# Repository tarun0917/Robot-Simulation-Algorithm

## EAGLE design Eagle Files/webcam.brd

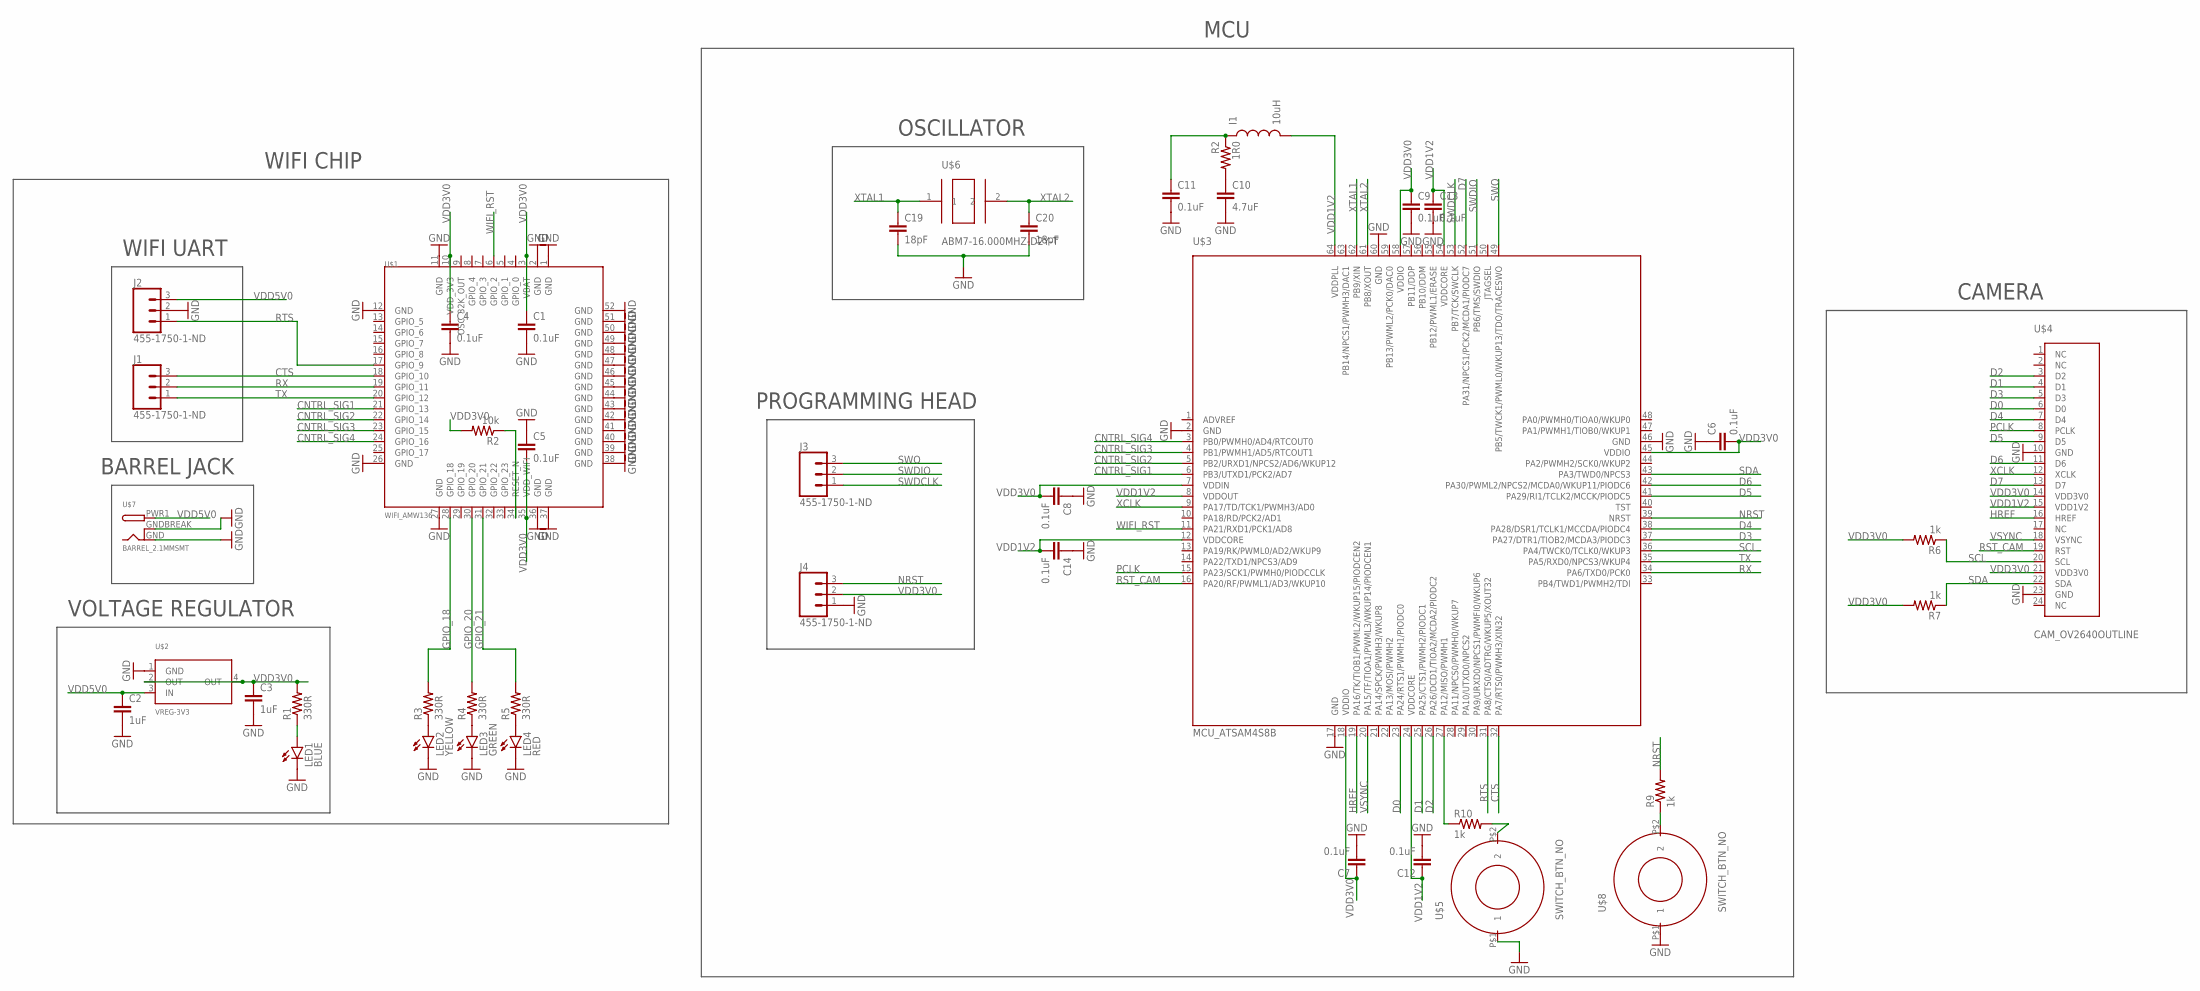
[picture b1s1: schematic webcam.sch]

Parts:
1R0: R2; 0805
C1, C4, C5, C6, C7, C8, C9, C11, C12, C13, C14: 0.1uF; 0805
C2, C3: 1uF; 0805
C10: 4.7uF; 0805
C19, C20: 18pF; 0805
I1: 10uH; 0805
J1, J2, J3, J4: 455-1750-1-ND; 1X03
LED1: BLUE; LED-0603
LED2: YELLOW; LED-0603
LED3: GREEN; LED-0603
LED4: RED; LED-0603
R1, R3, R4, R5: 330R; 0805
R2: 10k; 0805
R6, R7, R9, R10: 1k; 0805
U$1: WIFI_AMW136; AMW136
U$2: VREG-3V3; R-PDSO-G4_TI
U$3: MCU_ATSAM4S8B; QFP50P1200X1200X160-64N
U$4: CAM_OV2640OUTLINE; CAM_CONN
U$5, U$8: SWITCH_BTN_NO; BTN_2
U$6: ABM7-16.000MHZ-D2Y-T
U$7: BARREL_2.1MMSMT; DCJACK_2MM_SMT

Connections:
CNTRL_SIG1: U$1.21 (GPIO_13), U$3.6 (PB3/UTXD1/PCK2/AD7)
CNTRL_SIG2: U$1.22 (GPIO_14), U$3.5 (PB2/URXD1/NPCS2/AD6/WKUP12)
CNTRL_SIG3: U$1.23 (GPIO_15), U$3.4 (PB1/PWMH1/AD5/RTCOUT1)
CNTRL_SIG4: U$1.24 (GPIO_16), U$3.3 (PB0/PWMH0/AD4/RTCOUT0)
CTS: J1.3, U$1.18 (GPIO_10), U$3.32 (PA7/RTS0/PWMH3/XIN32)
D0: U$3.23 (PA24/RTS1/PWMH1/PIODC0), U$4.6 (D0)
D1: U$3.25 (PA25/CTS1/PWMH2/PIODC1), U$4.4 (D1)
D2: U$3.26 (PA26/DCD1/TIOA2/MCDA2/PIODC2), U$4.3 (D2)
D3: U$3.37 (PA27/DTR1/TIOB2/MCDA3/PIODC3), U$4.5 (D3)
D4: U$3.38 (PA28/DSR1/TCLK1/MCCDA/PIODC4), U$4.7 (D4)
D5: U$3.41 (PA29/RI1/TCLK2/MCCK/PIODC5), U$4.9 (D5)
D6: U$3.42 (PA30/PWML2/NPCS2/MCDA0/WKUP11/PIODC6), U$4.11 (D6)
D7: U$3.52 (PA31/NPCS1/PCK2/MCDA1/PIODC7), U$4.13 (D7)
GND: C1.2, C2.2, C3.2, C4.2, C5.1, C6.1, C7.2, C8.1, C9.2, C10.2, C11.2, C12.2, C13.2, C14.1, C19.2, C20.2, J2.2, J4.1, LED1.C, LED2.C, LED3.C, LED4.C, U$1.1 (GND), U$1.2 (GND), U$1.11 (GND), U$1.12 (GND), U$1.26 (GND), U$1.27 (GND), U$1.36 (GND), U$1.37 (GND), U$1.38 (GND), U$1.39 (GND), U$1.40 (GND), U$1.41 (GND), U$1.42 (GND), U$1.43 (GND), U$1.44 (GND), U$1.45 (GND), U$1.46 (GND), U$1.47 (GND), U$1.48 (GND), U$1.49 (GND), U$1.50 (GND), U$1.51 (GND), U$1.52 (GND), U$2.1 (GND), U$3.2 (GND), U$3.17 (GND), U$3.46 (GND), U$3.60 (GND), U$4.10 (GND), U$4.23 (GND), U$5.P$1 (1), U$7.GND, U$7.GNDBREAK, U$8.P$1 (1)
GPIO_18: R3.2, U$1.28 (GPIO_18)
GPIO_20: R4.2, U$1.30 (GPIO_20)
GPIO_21: R5.2, U$1.31 (GPIO_21)
HREF: U$3.19 (PA16/TK/TIOB1/PWML2/WKUP15/PIODCEN2), U$4.16 (HREF)
unnamed: LED1.A, R1.1
unnamed: 1R0.2, C10.1
unnamed: 1R0.1, C11.1, I1.1
unnamed: R10.1, U$3.27 (PA12/MISO/PWMH1)
unnamed: R10.2, U$5.P$2 (2)
unnamed: R9.1, U$8.P$2 (2)
unnamed: LED2.A, R3.1
unnamed: LED3.A, R4.1
unnamed: LED4.A, R5.1
unnamed: R2.1, U$1.34 (RESET_N)
NRST: J4.3, R9.2, U$3.39 (NRST)
PCLK: U$3.15 (PA23/SCK1/PWMH0/PIODCCLK), U$4.8 (PCLK)
RST_CAM: U$3.16 (PA20/RF/PWML1/AD3/WKUP10), U$4.19 (RST)
RTS: J2.1, U$1.17 (GPIO_9), U$3.31 (PA8/CTS0/ADTRG/WKUP5/XOUT32)
RX: J1.2, U$1.19 (GPIO_11), U$3.34 (PA6/TXD0/PCK0)
SCL: R6.1, U$3.36 (PA4/TWCK0/TCLK0/WKUP3), U$4.20 (SCL)
SDA: R7.1, U$3.43 (PA3/TWD0/NPCS3), U$4.22 (SDA)
SWDCLK: J3.1, U$3.53 (PB7/TCK/SWCLK)
SWDIO: J3.2, U$3.51 (PB6/TMS/SWDIO)
SWO: J3.3, U$3.49 (PB5/TWCK1/PWML0/WKUP13/TDO/TRACESWO)
TX: J1.1, U$1.20 (GPIO_12), U$3.35 (PA5/RXD0/NPCS3/WKUP4)
VDD1V2: C12.1, C13.1, C14.2, I1.2, U$3.8 (VDDOUT), U$3.12 (VDDCORE), U$3.24 (VDDCORE), U$3.54 (VDDCORE), U$3.64 (VDDPLL), U$4.15 (VDD1V2)
VDD3V0: C1.1, C3.1, C4.1, C5.2, C6.2, C7.1, C8.2, C9.1, J4.2, R1.2, R2.2, R6.2, R7.2, U$1.3 (VBAT), U$1.10 (VDD_3V3), U$1.35 (VDD_WIFI), U$2.2 (OUT), U$2.4 (OUT), U$3.7 (VDDIN), U$3.18 (VDDIO), U$3.45 (VDDIO), U$3.58 (VDDIO), U$4.14 (VDD3V0), U$4.21 (VDD3V0)
VDD5V0: C2.1, J2.3, U$2.3 (IN), U$7.PWR1 (PWR)
VSYNC: U$3.20 (PA15/TF/TIOA1/PWML3/WKUP14/PIODCEN1), U$4.18 (VSYNC)
WIFI_RST: U$1.6 (GPIO_2), U$3.11 (PA21/RXD1/PCK1/AD8)
XCLK: U$3.9 (PA17/TD/TCK1/PWMH3/AD0), U$4.12 (XCLK)
XTAL1: C19.1, U$3.62 (PB9/XIN), U$6.1
XTAL2: C20.1, U$3.61 (PB8/XOUT), U$6.2

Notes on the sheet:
OSCILLATOR
CAMERA
PROGRAMMING HEAD
VOLTAGE REGULATOR
BARREL JACK
WIFI UART
MCU
WIFI CHIP

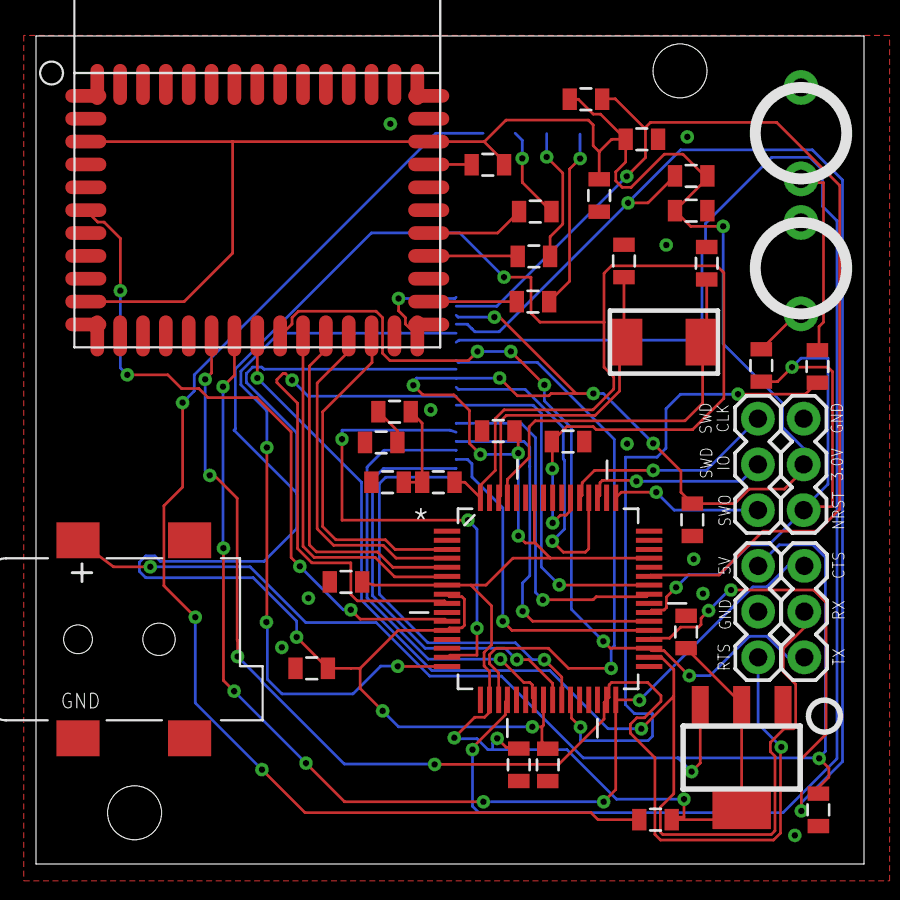
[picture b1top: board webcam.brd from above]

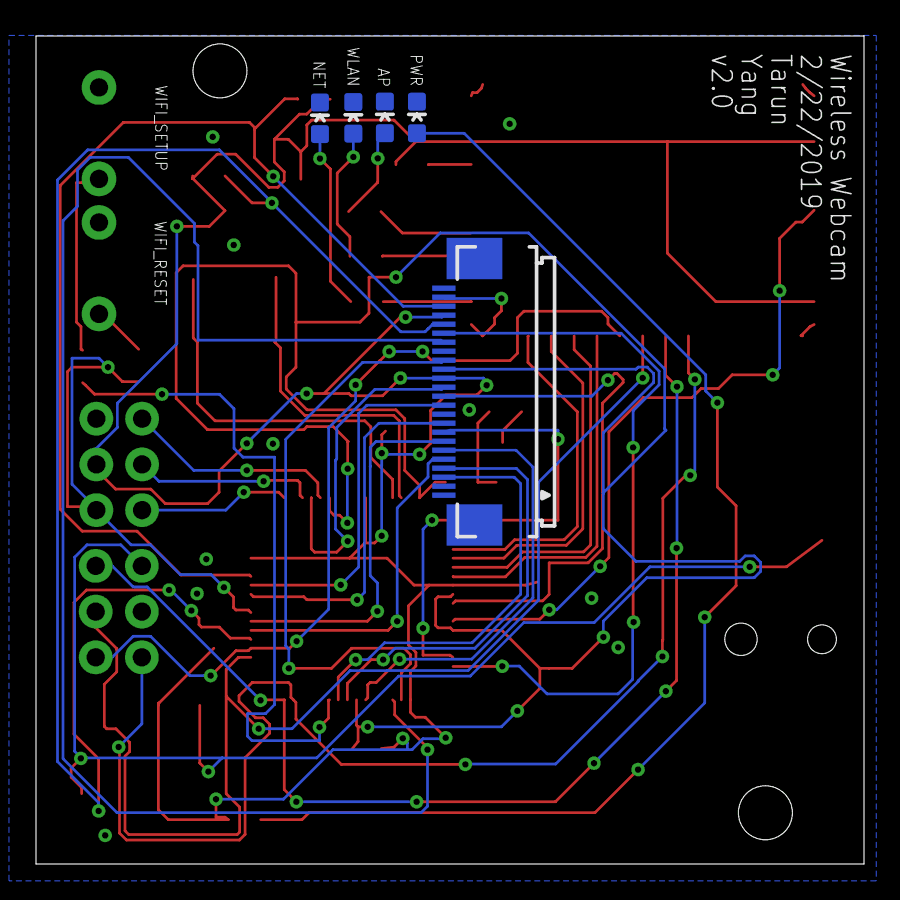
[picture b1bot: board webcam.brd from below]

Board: 2 copper layers, 46.0 x 46.0 mm, 43 parts (5 on the bottom side), 47 nets.

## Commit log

2018-04-19 Second Commit
2019-08-01 Added Eagle Files

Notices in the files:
parts and their libraries:
SparkFun: Licensing: CC v3.0 Share-Alike You are welcome to use this library for commercial purposes.
SparkFun-Connectors: Licensing: Creative Commons ShareAlike 4.0 International - https://creativecommons.org/licenses/by-sa/4.0
